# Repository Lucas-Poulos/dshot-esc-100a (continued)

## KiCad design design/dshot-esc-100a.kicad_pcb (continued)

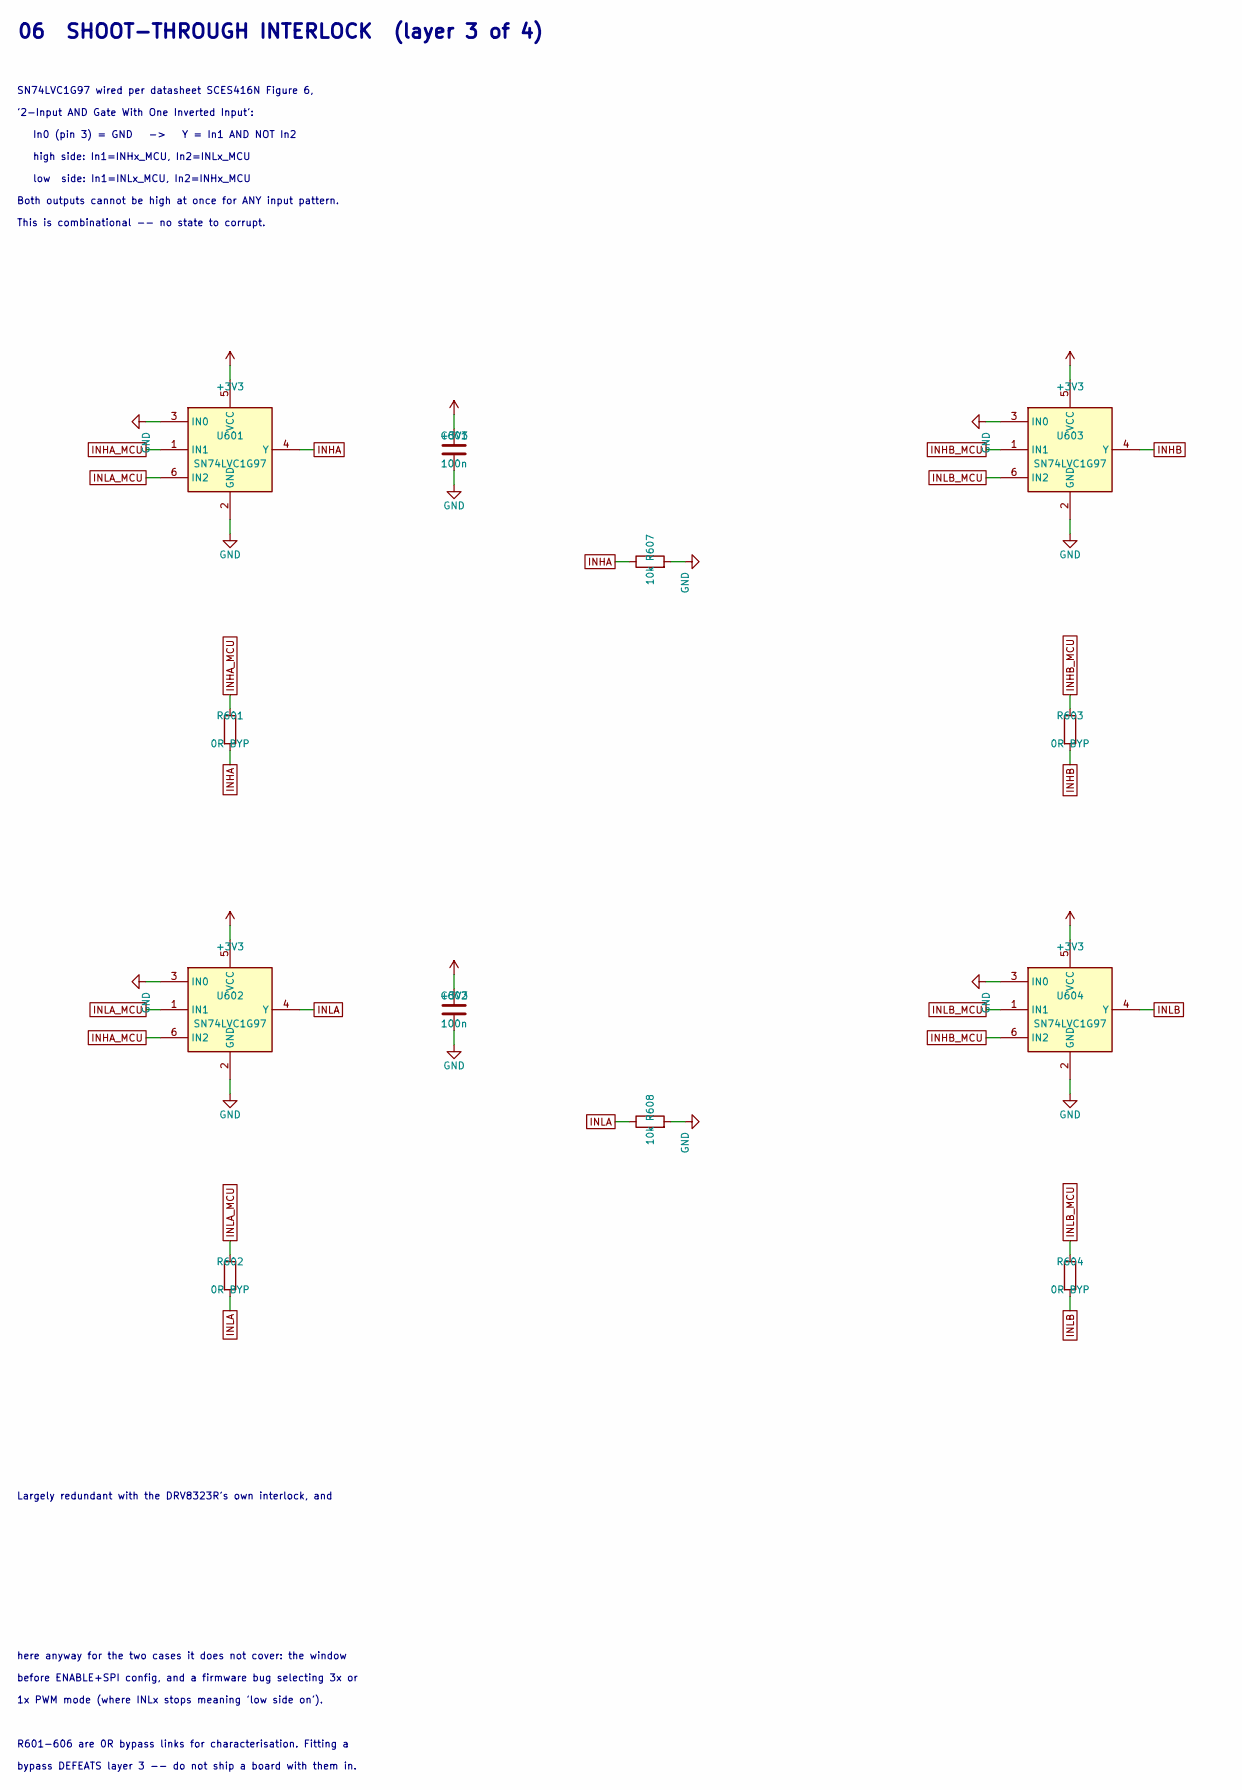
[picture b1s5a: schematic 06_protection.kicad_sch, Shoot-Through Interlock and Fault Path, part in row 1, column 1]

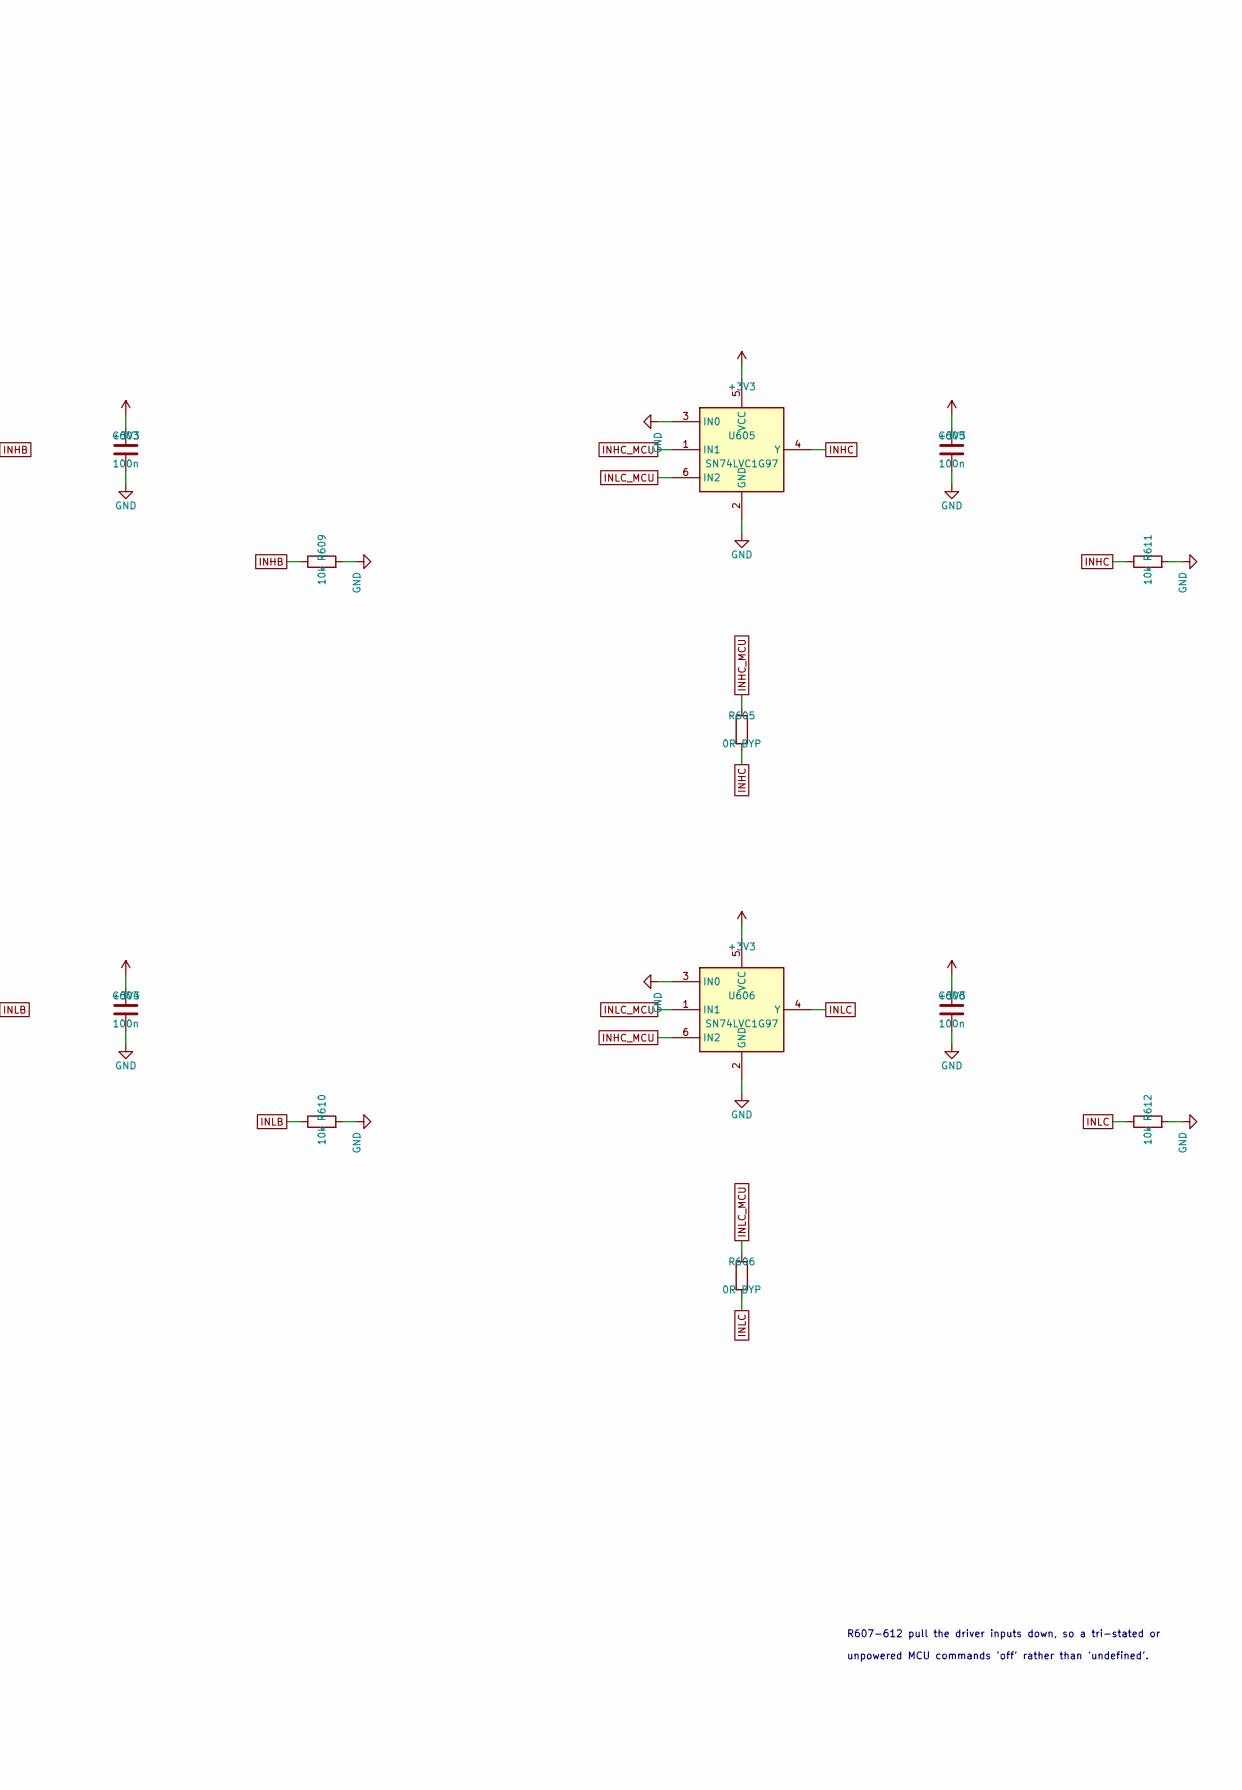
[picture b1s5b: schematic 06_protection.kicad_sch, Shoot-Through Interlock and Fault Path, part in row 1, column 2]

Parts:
C601, C602, C603, C604, C605, C606: 100n; C_0603_1608Metric; MPN CC0603KRX7R9BB104; LCSC C14663
R601, R602, R603, R604, R605, R606: 0R BYP; R_0603_1608Metric; MPN RCA030RLF; LCSC C22356631
R607, R608, R609, R610, R611, R612: 10k; R_0603_1608Metric; MPN FRC0603F1002TS; LCSC C2906982
U601, U602, U603, U604, U605, U606: SN74LVC1G97; SOT-23-6; MPN SN74LVC1G97DBVR; LCSC C128411

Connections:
+3V3: C601.1, C602.1, C603.1, C604.1, C605.1, C606.1, U601.5 (VCC), U602.5 (VCC), U603.5 (VCC), U604.5 (VCC), U605.5 (VCC), U606.5 (VCC); also elsewhere on the board
GND: C601.2, C602.2, C603.2, C604.2, C605.2, C606.2, R607.2, R608.2, R609.2, R610.2, R611.2, R612.2, U601.2 (GND), U601.3 (IN0), U602.2 (GND), U602.3 (IN0), U603.2 (GND), U603.3 (IN0), U604.2 (GND), U604.3 (IN0), U605.2 (GND), U605.3 (IN0), U606.2 (GND), U606.3 (IN0); also elsewhere on the board
INHA: R601.2, R607.1, U601.4 (Y); also elsewhere on the board
INHA_MCU: R601.1, U601.1 (IN1), U602.6 (IN2); also elsewhere on the board
INHB: R603.2, R609.1, U603.4 (Y); also elsewhere on the board
INHB_MCU: R603.1, U603.1 (IN1), U604.6 (IN2); also elsewhere on the board
INHC: R605.2, R611.1, U605.4 (Y); also elsewhere on the board
INHC_MCU: R605.1, U605.1 (IN1), U606.6 (IN2); also elsewhere on the board
INLA: R602.2, R608.1, U602.4 (Y); also elsewhere on the board
INLA_MCU: R602.1, U601.6 (IN2), U602.1 (IN1); also elsewhere on the board
INLB: R604.2, R610.1, U604.4 (Y); also elsewhere on the board
INLB_MCU: R604.1, U603.6 (IN2), U604.1 (IN1); also elsewhere on the board
INLC: R606.2, R612.1, U606.4 (Y); also elsewhere on the board
INLC_MCU: R606.1, U605.6 (IN2), U606.1 (IN1); also elsewhere on the board

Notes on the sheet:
high side: In1=INHx_MCU, In2=INLx_MCU
low side: In1=INLx_MCU, In2=INHx_MCU
before ENABLE+SPI config, and a firmware bug selecting 3x or
Largely redundant with the DRV8323R's own interlock, and
R601-606 are 0R bypass links for characterisation. Fitting a
06 SHOOT-THROUGH INTERLOCK (layer 3 of 4)
SN74LVC1G97 wired per datasheet SCES416N Figure 6,
bypass DEFEATS layer 3 -- do not ship a board with them in.
'2-Input AND Gate With One Inverted Input':
1x PWM mode (where INLx stops meaning 'low side on').
This is combinational -- no state to corrupt.
Both outputs cannot be high at once for ANY input pattern.
here anyway for the two cases it does not cover: the window
unpowered MCU commands 'off' rather than 'undefined'.
In0 (pin 3) = GND -> Y = In1 AND NOT In2
R607-612 pull the driver inputs down, so a tri-stated or

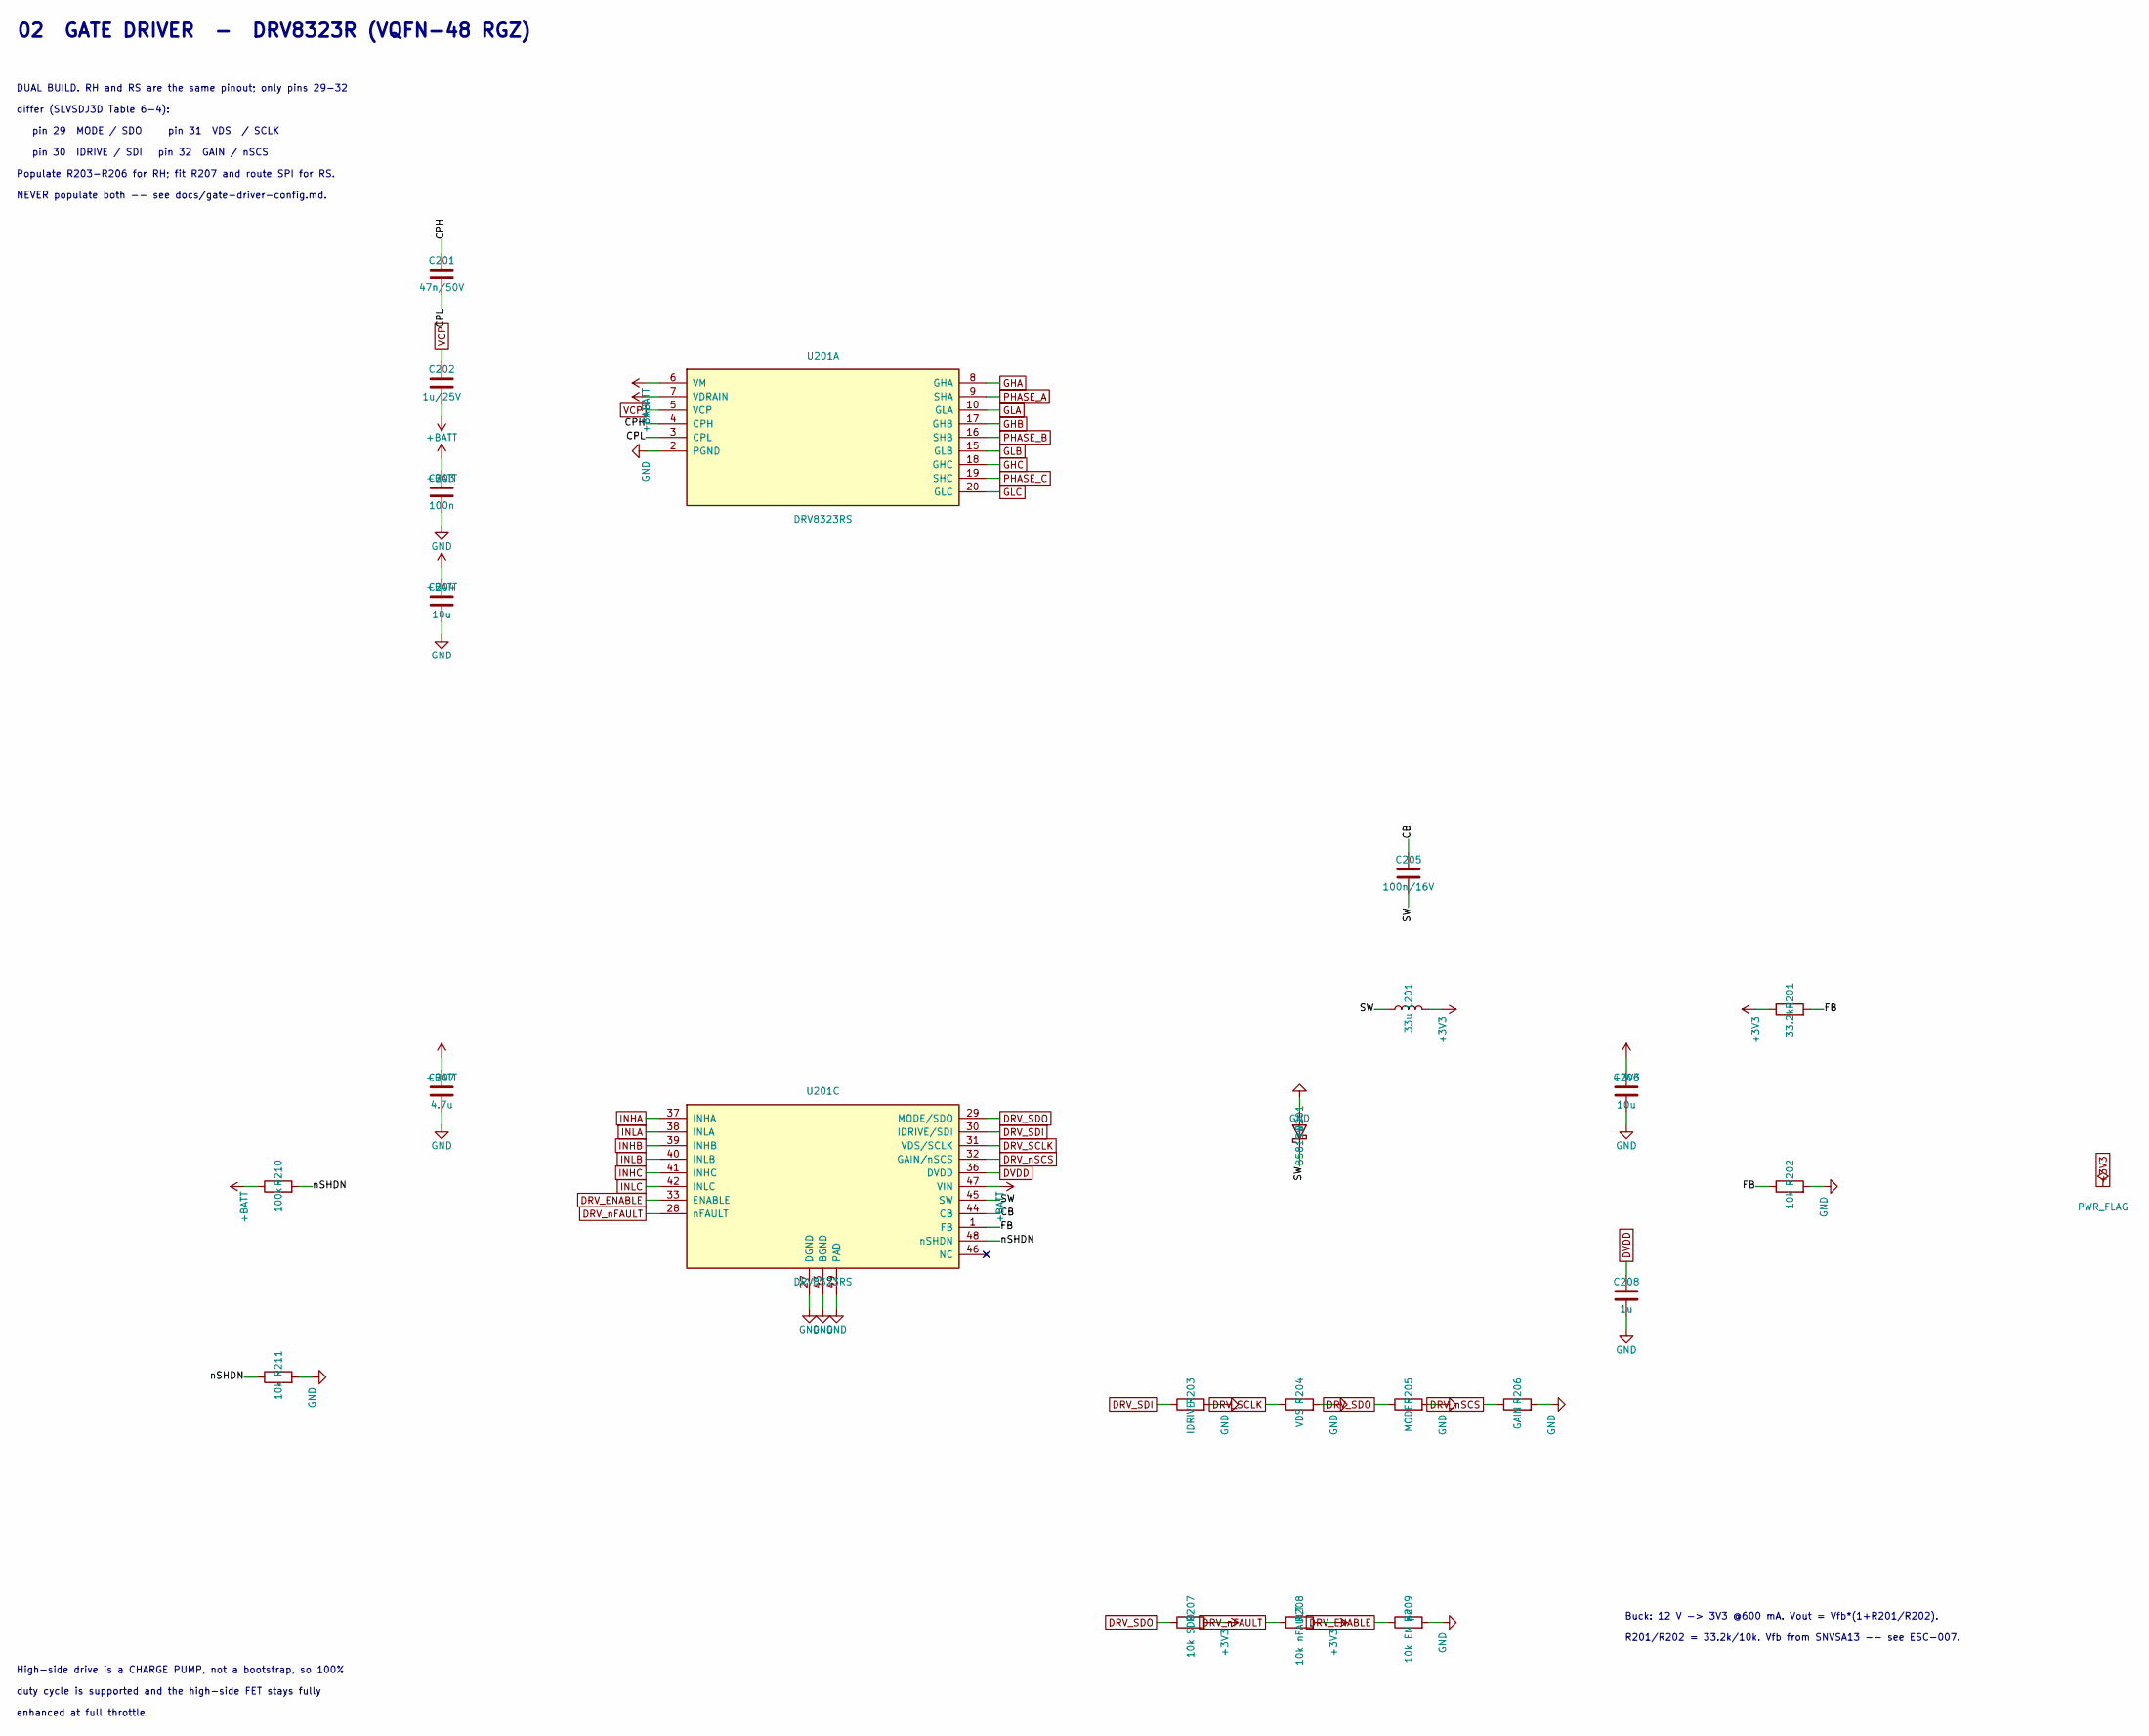
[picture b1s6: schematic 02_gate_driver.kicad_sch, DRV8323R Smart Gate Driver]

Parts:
C201: 47n/50V; C_0603_1608Metric; MPN CL10B473KB8NNNC; LCSC C1622
C202: 1u/25V; C_0603_1608Metric; MPN CL10B105KA8NNNC; LCSC C29936
C203: 100n; C_0603_1608Metric; MPN CC0603KRX7R9BB104; LCSC C14663
C204, C206: 10u; C_1210_3225Metric; MPN GRM32DR71E106KA12L; LCSC C77100
C205: 100n/16V; C_0603_1608Metric; MPN CC0603KRX7R9BB104; LCSC C14663
C207: 4.7u; C_0805_2012Metric; MPN CL21B475KAFNNNE; LCSC C98195
C208: 1u; C_0603_1608Metric; MPN CL10B105KA8NNNC; LCSC C29936
D201: B5819W; D_SOD-123; MPN B5819W SL; LCSC C8598
L201: 33u; L_7.3x7.3_H3.5; MPN SLS6D38S330MTT; LCSC C364136
R201: 33.2k; R_0603_1608Metric; MPN FRC0603F3322TS; LCSC C2933200
R202, R211: 10k; R_0603_1608Metric; MPN FRC0603F1002TS; LCSC C2906982
R203: IDRIVE; R_0603_1608Metric; MPN FRC0603F1002TS; LCSC C2906982
R204: VDS; R_0603_1608Metric; MPN FRC0603F1002TS; LCSC C2906982
R205: MODE; R_0603_1608Metric; MPN FRC0603F1002TS; LCSC C2906982
R206: GAIN; R_0603_1608Metric; MPN FRC0603F1002TS; LCSC C2906982
R207: 10k SDO; R_0603_1608Metric; MPN FRC0603F1002TS; LCSC C2906982
R208: 10k nFAULT; R_0603_1608Metric; MPN FRC0603F1002TS; LCSC C2906982
R209: 10k EN pd; R_0603_1608Metric; MPN FRC0603F1002TS; LCSC C2906982
R210: 100k; R_0603_1608Metric; MPN 0603WAF1003T5E; LCSC C25803
U201: DRV8323RS; Texas_RGZ0048A_VQFN-48-1EP_7x7mm_P0.5mm_EP5.15x5.15mm; MPN DRV8323RSRGZT; LCSC C2653553

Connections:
+3V3: C206.1, L201.2, R201.1, R207.2, R208.2; also elsewhere on the board
+BATT: C202.2, C203.1, C204.1, C207.1, R210.1, U201.6 (VM), U201.7 (VDRAIN), U201.47 (VIN); also elsewhere on the board
/Gate Driver/CB: C205.1, U201.44 (CB)
/Gate Driver/CPH: C201.1, U201.4 (CPH)
/Gate Driver/CPL: C201.2, U201.3 (CPL)
/Gate Driver/FB: R201.2, R202.1, U201.1 (FB)
/Gate Driver/SW: C205.2, D201.1 (K), L201.1, U201.45 (SW)
/Gate Driver/nSHDN: R210.2, R211.1, U201.48 (nSHDN)
DRV_ENABLE: R209.1, U201.33 (ENABLE); also elsewhere on the board
DRV_SCLK: R204.1, U201.31 (VDS/SCLK); also elsewhere on the board
DRV_SDI: R203.1, U201.30 (IDRIVE/SDI); also elsewhere on the board
DRV_SDO: R205.1, R207.1, U201.29 (MODE/SDO); also elsewhere on the board
DRV_nFAULT: R208.1, U201.28 (nFAULT); also elsewhere on the board
DRV_nSCS: R206.1, U201.32 (GAIN/nSCS); also elsewhere on the board
DVDD: C208.1, U201.36 (DVDD)
GHA: U201.8 (GHA); also elsewhere on the board
GHB: U201.17 (GHB); also elsewhere on the board
GHC: U201.18 (GHC); also elsewhere on the board
GLA: U201.10 (GLA); also elsewhere on the board
GLB: U201.15 (GLB); also elsewhere on the board
GLC: U201.20 (GLC); also elsewhere on the board
GND: C203.2, C204.2, C206.2, C207.2, C208.2, D201.2 (A), R202.2, R203.2, R204.2, R205.2, R206.2, R209.2, R211.2, U201.2 (PGND), U201.27 (DGND), U201.43 (BGND), U201.49 (PAD); also elsewhere on the board
INHA: U201.37 (INHA); also elsewhere on the board
INHB: U201.39 (INHB); also elsewhere on the board
INHC: U201.41 (INHC); also elsewhere on the board
INLA: U201.38 (INLA); also elsewhere on the board
INLB: U201.40 (INLB); also elsewhere on the board
INLC: U201.42 (INLC); also elsewhere on the board
PHASE_A: U201.9 (SHA); also elsewhere on the board
PHASE_B: U201.16 (SHB); also elsewhere on the board
PHASE_C: U201.19 (SHC); also elsewhere on the board
VCP: C202.1, U201.5 (VCP)

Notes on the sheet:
Populate R203-R206 for RH; fit R207 and route SPI for RS.
DUAL BUILD. RH and RS are the same pinout; only pins 29-32
Buck: 12 V -> 3V3 @600 mA. Vout = Vfb*(1+R201/R202).
differ (SLVSDJ3D Table 6-4):
02 GATE DRIVER - DRV8323R (VQFN-48 RGZ)
pin 29 MODE / SDO pin 31 VDS / SCLK
R201/R202 = 33.2k/10k. Vfb from SNVSA13 -- see ESC-007.
enhanced at full throttle.
NEVER populate both -- see docs/gate-driver-config.md.
duty cycle is supported and the high-side FET stays fully
High-side drive is a CHARGE PUMP, not a bootstrap, so 100%
pin 30 IDRIVE / SDI pin 32 GAIN / nSCS

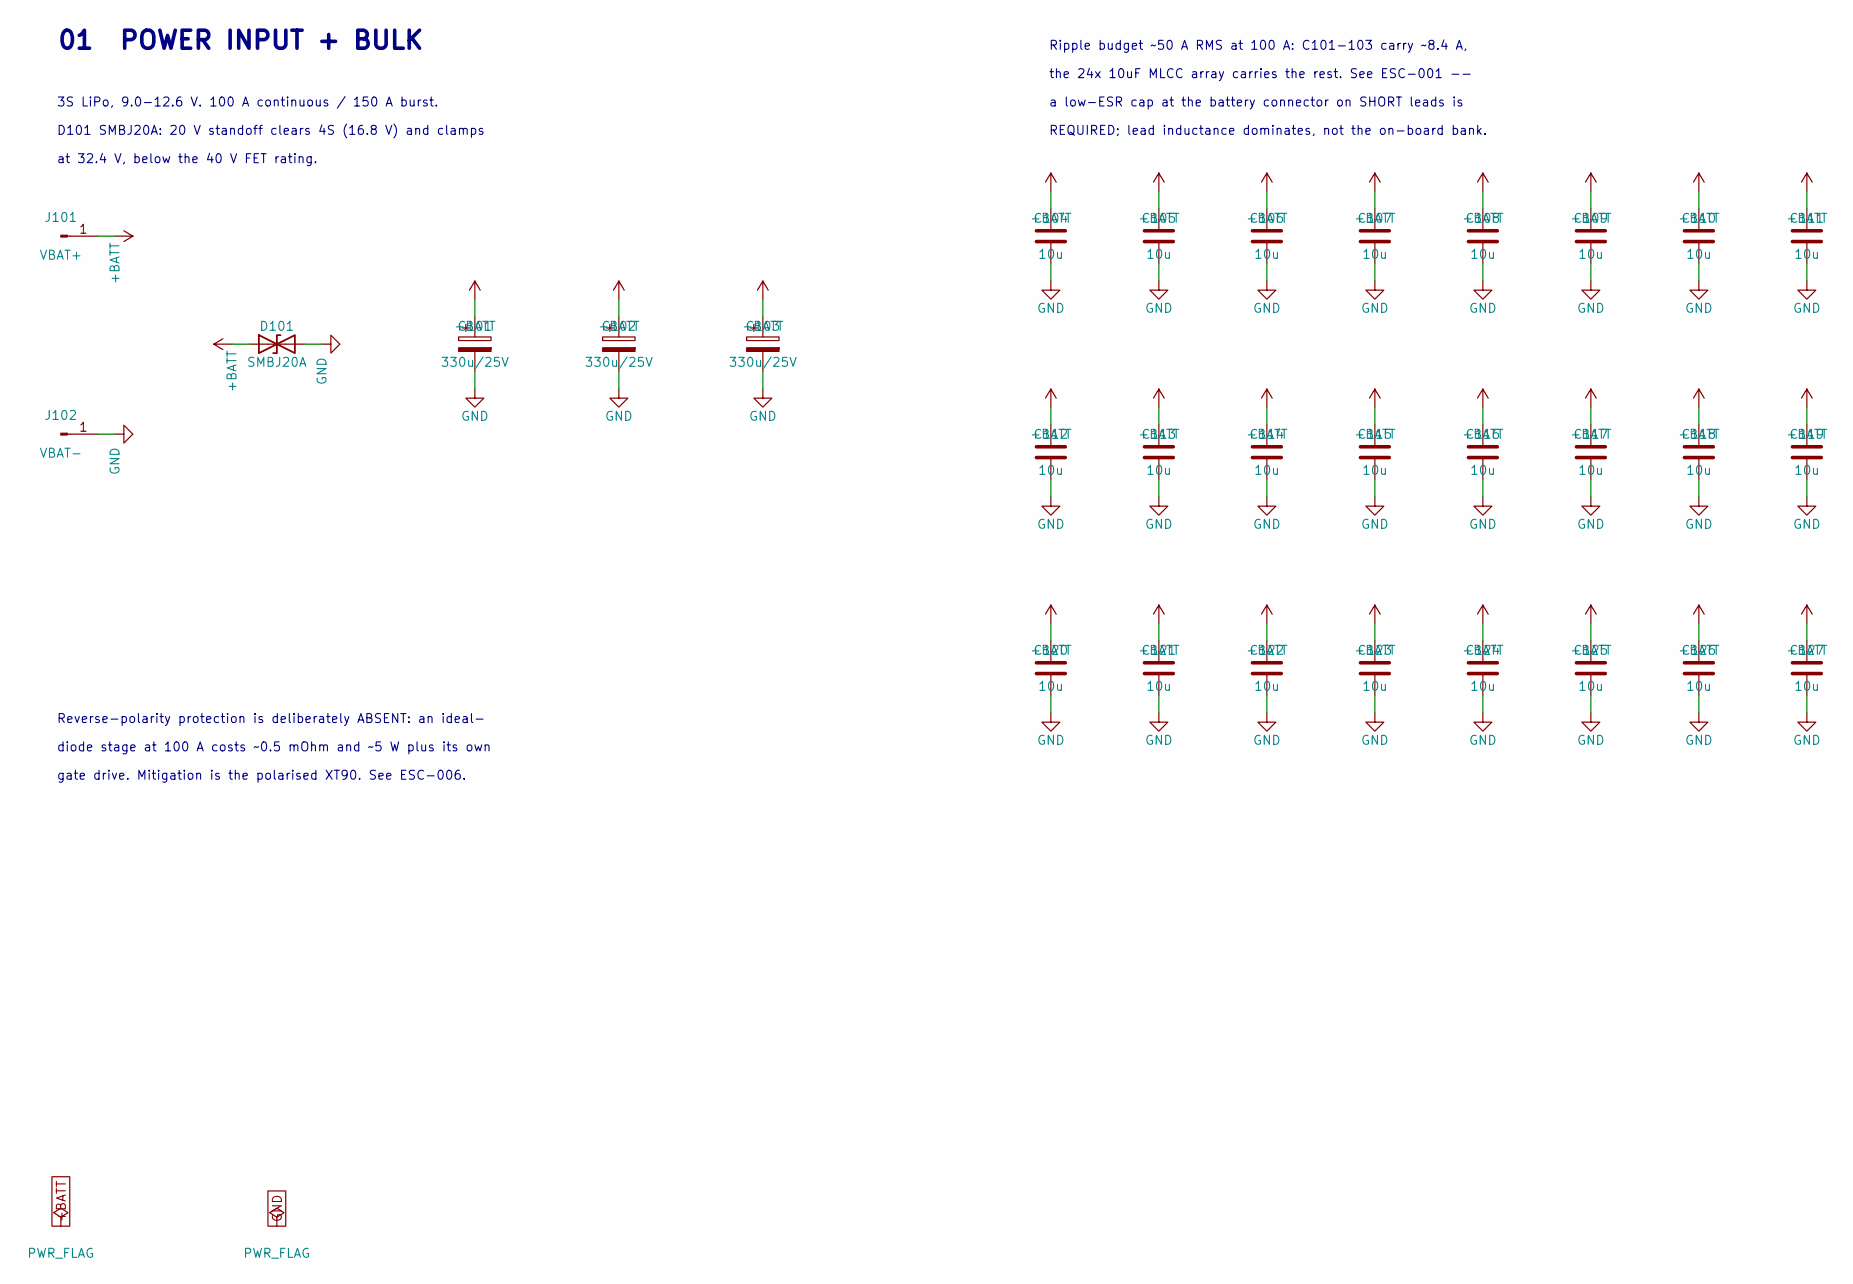
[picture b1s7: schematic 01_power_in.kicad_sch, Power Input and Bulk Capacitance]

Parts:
C101, C102, C103: 330u/25V; CP_Radial_D8.0mm_P3.50mm; MPN SPZ1EM331F11O00R; LCSC C160677
C104, C105, C106, C107, C108, C109, C110, C111, C112, C113, C114, C115, C116, C117, C118, C119, C120, C121, C122, C123, C124, C125, C126, C127: 10u; C_1210_3225Metric; MPN GRM32DR71E106KA12L; LCSC C77100
D101: SMBJ20A; D_SMB; MPN SMBJ20A; LCSC C364296
J101: VBAT+; HighCurrentTerminal_8AWG
J102: VBAT-; HighCurrentTerminal_8AWG

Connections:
+BATT: C101.1, C102.1, C103.1, C104.1, C105.1, C106.1, C107.1, C108.1, C109.1, C110.1, C111.1, C112.1, C113.1, C114.1, C115.1, C116.1, C117.1, C118.1, C119.1, C120.1, C121.1, C122.1, C123.1, C124.1, C125.1, C126.1, C127.1, D101.1 (A1), J101.1; also elsewhere on the board
GND: C101.2, C102.2, C103.2, C104.2, C105.2, C106.2, C107.2, C108.2, C109.2, C110.2, C111.2, C112.2, C113.2, C114.2, C115.2, C116.2, C117.2, C118.2, C119.2, C120.2, C121.2, C122.2, C123.2, C124.2, C125.2, C126.2, C127.2, D101.2 (A2), J102.1; also elsewhere on the board

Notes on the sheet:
Reverse-polarity protection is deliberately ABSENT: an ideal-
gate drive. Mitigation is the polarised XT90. See ESC-006.
at 32.4 V, below the 40 V FET rating.
a low-ESR cap at the battery connector on SHORT leads is
3S LiPo, 9.0-12.6 V. 100 A continuous / 150 A burst.
01 POWER INPUT + BULK
REQUIRED; lead inductance dominates, not the on-board bank.
Ripple budget ~50 A RMS at 100 A: C101-103 carry ~8.4 A,
diode stage at 100 A costs ~0.5 mOhm and ~5 W plus its own
the 24x 10uF MLCC array carries the rest. See ESC-001 --
D101 SMBJ20A: 20 V standoff clears 4S (16.8 V) and clamps

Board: 4 copper layers, 160 parts (53 on the bottom side), 72 nets, no tracks yet.

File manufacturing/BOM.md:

# Bill of materials

Generated from the schematic netlist by `scripts/gen_bom.py` on 2026-09-25. Do not edit by hand -- regenerate.

**43 distinct lines, 160 placements.** The schematic is fully wired and ERC-clean, so these quantities are real rather than provisional.

Prices and stock are deliberately absent -- they go stale within days. Refresh before a BOM lock with the `lcsc` skill.

---

## Sourcing notes

**The gate driver is the line to watch.** The design is laid out for both DRV8323R variants on one footprint -- only pins 29-32 differ (SLVSDJ3D Table 6-4):

| Part | LCSC | Stock | Price | Configured by |
|---|---|---:|---:|---|
| `DRV8323RSRGZT` | C2653553 | ~67 | $4.29 | SPI, from the MCU |
| `DRV8323RHRGZR` | C543035 | ~2338 | $2.39 | resistors R203-R206 |

RS is the default because it can set source and sink gate current independently, which is what produces the turn-off/turn-on asymmetry the dead-time budget relies on. RH cannot -- one pin sets both. An RH build is still safe but has less margin, and its resistor values are **not yet transcribed** (issue ESC-010). See `docs/gate-driver-config.md` before substituting.

Everything else is commodity: no part below has under ~1000 pieces at LCSC, and the FETs, MCU and logic all have multiple sources.

---

## Lines

| Qty | MPN | LCSC | Value | Package | Refs | Sheets |
|----:|-----|------|-------|---------|------|--------|
| 29 | `FRC0603F1002TS` | `C2906982` | 10k | R_0603_1608Metric | R202, R211, R313, R314, ... (+25) | Gate Driver, MCU, Power Stage, Protection, Sense |
| 26 | `GRM32DR71E106KA12L` | `C77100` | 10u | C_1210_3225Metric | C104, C105, C106, C107, ... (+22) | Gate Driver, Power Input |
| 12 | `FRC0805F4R70TS` | `C2933459` | 4.7 | R_0805_2012Metric | R301, R302, R303, R304, ... (+8) | Power Stage |
| 12 | `TPHR8504PL,L1Q(M` | `C5331611` | TPHR8504PL | PQFN-8-EP_6x5mm_P1.27mm_Generic | Q301, Q302, Q303, Q304, ... (+8) | Power Stage |
| 11 | `CC0603KRX7R9BB104` | `C14663` | 100n | C_0603_1608Metric | C203, C401, C402, C501, ... (+7) | Gate Driver, MCU, Protection, Sense |
| 7 | `B5819W SL` | `C8598` | B5819W | D_SOD-123 | D201, D301, D302, D303, D304, D305, D306 | Gate Driver, Power Stage |
| 6 | `RCA030RLF` | `C22356631` | 0 | R_0603_1608Metric | R325, R326, R327, R328, R329, R330 | Power Stage |
| 6 | `RCA030RLF` | `C22356631` | 0R BYP | R_0603_1608Metric | R601, R602, R603, R604, R605, R606 | Protection |
| 6 | `SN74LVC1G97DBVR` | `C128411` | SN74LVC1G97 | SOT-23-6 | U601, U602, U603, U604, U605, U606 | Protection |
| 5 | `FRC0603F1001TS` | `C2907002` | 1k | R_0603_1608Metric | R402, R504, R505, R506, R510 | MCU, Sense |
| 4 | `HoJLR2512-3W-1mR-1%` | `C2903470` | 1m | R_2512_6332Metric | RS301, RS302, RS303, RS304 | Power Stage |
| 3 | `SPZ1EM331F11O00R` | `C160677` | 330u/25V | CP_Radial_D8.0mm_P3.50mm | C101, C102, C103 | Power Input |
| 2 | `0603WAF1003T5E` | `C25803` | 100k | R_0603_1608Metric | R210, R511 | Gate Driver, Sense |
| 2 | `CL21B475KAFNNNE` | `C98195` | 4.7u | C_0805_2012Metric | C207, C403 | Gate Driver, MCU |
| 1 | `-` | `-` | PHASE_A | SolderWire-2.5sqmm_1x01_D2.4mm_OD3.6mm_Relief | J301 | Power Stage |
| 1 | `-` | `-` | PHASE_B | SolderWire-2.5sqmm_1x01_D2.4mm_OD3.6mm_Relief | J302 | Power Stage |
| 1 | `-` | `-` | PHASE_C | SolderWire-2.5sqmm_1x01_D2.4mm_OD3.6mm_Relief | J303 | Power Stage |
| 1 | `-` | `-` | SWD | PinHeader_2x05_P1.27mm_Vertical | J401 | MCU |
| 1 | `-` | `-` | SIGNAL | PinHeader_1x04_P2.54mm_Vertical | J402 | MCU |
| 1 | `-` | `-` | VBAT+ | SolderWire-2.5sqmm_1x01_D2.4mm_OD3.6mm_Relief | J101 | Power Input |
| 1 | `-` | `-` | VBAT- | SolderWire-2.5sqmm_1x01_D2.4mm_OD3.6mm_Relief | J102 | Power Input |
| 1 | `CC0603KRX7R9BB104` | `C14663` | 100n/16V | C_0603_1608Metric | C205 | Gate Driver |
| 1 | `CC0603KRX7R9BB104` | `C14663` | 100n VREF+ | C_0603_1608Metric | C404 | MCU |
| 1 | `CC0603KRX7R9BB104` | `C14663` | 100n NRST | C_0603_1608Metric | C406 | MCU |
| 1 | `CC0603KRX7R9BB104` | `C14663` | 100n VREF | C_0603_1608Metric | C503 | Sense |
| 1 | `CL10B105KA8NNNC` | `C29936` | 1u/25V | C_0603_1608Metric | C202 | Gate Driver |
| 1 | `CL10B105KA8NNNC` | `C29936` | 1u | C_0603_1608Metric | C208 | Gate Driver |
| 1 | `CL10B105KA8NNNC` | `C29936` | 1u VREF+ | C_0603_1608Metric | C405 | MCU |
| 1 | `CL10B473KB8NNNC` | `C1622` | 47n/50V | C_0603_1608Metric | C201 | Gate Driver |
| 1 | `DRV8323RSRGZT` | `C2653553` | DRV8323RS | Texas_RGZ0048A_VQFN-48-1EP_7x7mm_P0.5mm_EP5.15x5.15mm_ThermalVias | U201 | Gate Driver |
| 1 | `FRC0603F1002TS` | `C2906982` | IDRIVE | R_0603_1608Metric | R203 | Gate Driver |
| 1 | `FRC0603F1002TS` | `C2906982` | VDS | R_0603_1608Metric | R204 | Gate Driver |
| 1 | `FRC0603F1002TS` | `C2906982` | MODE | R_0603_1608Metric | R205 | Gate Driver |
| 1 | `FRC0603F1002TS` | `C2906982` | GAIN | R_0603_1608Metric | R206 | Gate Driver |
| 1 | `FRC0603F1002TS` | `C2906982` | 10k SDO | R_0603_1608Metric | R207 | Gate Driver |
| 1 | `FRC0603F1002TS` | `C2906982` | 10k nFAULT | R_0603_1608Metric | R208 | Gate Driver |
| 1 | `FRC0603F1002TS` | `C2906982` | 10k EN pd | R_0603_1608Metric | R209 | Gate Driver |
| 1 | `FRC0603F3322TS` | `C2933200` | 33.2k | R_0603_1608Metric | R201 | Gate Driver |
| 1 | `NCP18XH103F03RB` | `C13564` | 10k NTC | R_0603_1608Metric | R513 | Sense |
| 1 | `SLS6D38S330MTT` | `C364136` | 33u | L_7.3x7.3_H3.5 | L201 | Gate Driver |
| 1 | `SMBJ20A` | `C364296` | SMBJ20A | D_SMB | D101 | Power Input |
| 1 | `STM32G071CBT6` | `C432212` | STM32G071CBT6 | LQFP-48_7x7mm_P0.5mm | U401 | MCU |
| 1 | `XL-1608UGC-04` | `C965804` | green | LED_0603_1608Metric | D401 | MCU |

---

## Lines needing attention

| MPN | Note |
|---|---|
| `GRM32DR71E106KA12L` | 24 off. Derates to ~5-6 uF at 12 V bias - ESC-001 |
| `TPHR8504PL,L1Q(M` | 12 off, 2 per switch position. 40 V on a 12.6 V bus is deliberate - see docs/architecture.md |
| `SN74LVC1G97DBVR` | Shoot-through interlock. Wired per SCES416N Fig 6 |
| `HoJLR2512-3W-1mR-1%` | 4 in parallel = 0.25 mOhm. Needs a Kelvin sense tap in layout - ESC-005 |
| `SPZ1EM331F11O00R` | Through-hole radial. ~2.8 A ripple each - ESC-001 |
| `DRV8323RSRGZT` | SPI variant. RH (C543035) is pin-compatible - see docs/gate-driver-config.md before substituting |
| `STM32G071CBT6` | 48-pin part is REQUIRED: it is the only one that frees PB12/TIM1_BKIN. Symbol is KiCad's G081CBTx renamed |

## Before ordering

1. Wire the schematic -- quantities here are pre-wiring estimates.
2. Refresh stock for every line; flag anything under 10x requirement.
3. Record a second-source C-number for each thin line in that part's `manufacturing/parts/{Vendor}/{MPN}/{MPN}.md`.
4. Resolve everything in `manufacturing/stm32mp157-devkit/ISSUES.md` or defer it explicitly.
5. Re-run `python3 scripts/verify_project.py`.
6. Re-check stock immediately before placing the order -- do not order against numbers from a previous session.

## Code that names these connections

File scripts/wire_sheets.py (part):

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def wire_04_mcu(sheet: Sheet, cache: SymbolCache) -> None:
    """Pins are addressed by NUMBER, not name.

    PA9 and PA10 each appear twice in the 48-pin symbol -- as the dedicated
    pins 29/32 and again as the remappable PA11/PA12 pads 33/34. Addressing
    by name would be ambiguous, and picking the wrong one puts a PWM output
    on an unbonded pad.
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    w.power("R401", "1", V3V3)

    # --- TIM1 complementary PWM -> interlock (sheet 06) ---
    w.rail(INH_MCU["A"], (M, "32"))                               # PA10 TIM1_CH3
    w.rail(INL_MCU["A"], (M, "20"))                               # PB1  TIM1_CH3N
    w.rail(INH_MCU["B"], (M, "29"))                               # PA9  TIM1_CH2
    w.rail(INL_MCU["B"], (M, "19"))                               # PB0  TIM1_CH2N
    w.rail(INH_MCU["C"], (M, "28"))                               # PA8  TIM1_CH1
    w.rail(INL_MCU["C"], (M, "18"))                               # PA7  TIM1_CH1N
    # PA11 / PA12 pads are unused because NO_PA11_PA12_REMAP is set
    w.no_connect(M, "33")
    w.no_connect(M, "34")

    # --- sensorless comparator inputs ---
    w.rail(BEMF["A"], (M, "46"))       # PB7 COMP2_INM IO2
    w.rail(BEMF["B"], (M, "42"))       # PB3 COMP2_INM IO1
    w.rail(BEMF["C"], (M, "13"))       # PA2 COMP2_INM IO3
    w.rail(V_NEUTRAL, (M, "14"))       # PA3 COMP2_INP IO3

    # --- ADC ---
    w.rail(ADC_BUSV, (M, "15"))      # PA4 ADC_IN4
    w.rail(ADC_CURRENT, (M, "17"))         # PA6 ADC_IN6
    w.rail(ADC_TEMP, (M, "12"))       # PA1 ADC_IN1

    # --- gate driver control ---
    w.rail(DRV_NSCS, (M, "11"))        # PA0
    w.rail(DRV_SDO, (M, "21"))         # PB2
    w.rail(DRV_SCLK, (M, "22"))        # PB10
    w.rail(DRV_SDI, (M, "23"))         # PB11
    w.rail(DRV_NFAULT, (M, "24"))      # PB12 TIM1_BKIN
    w.rail(DRV_ENABLE, (M, "25"))      # PB13
    w.rail(DRV_CAL, (M, "26"))         # PB14

    # --- host interface + debug ---
    w.rail(DSHOT_IN, (M, "43"))        # PB4 TIM3_CH1 + DMA1_CH1
    w.rail(TELEM, (M, "45"))           # PB6 USART1 AF0, one-wire
    w.rail(SWDIO, (M, "35"))           # PA13
    w.rail(SWCLK, (M, "36"))           # PA14
    w.rail(LED_STATUS, (M, "30"))      # PC6

    # unused pins
    for pin in ("1", "2", "3", "8", "9", "16", "27", "31", "37",
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
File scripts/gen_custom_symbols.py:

#!/usr/bin/env python3
"""Generate the project-local symbol library: design/lib/dshot-esc-100a.kicad_sym

Two symbols, for two different reasons.

DRV8323R
    KiCad 10 ships no DRV83xx smart gate driver at all (Driver_Motor has
    DRV8308/8311/8412/8434/8461 and nothing else), so this is built from
    scratch. Every pin below is transcribed from **Table 6-4, "Pin
    Functions - 48-Pin DRV8323R Devices"** of the DRV832x datasheet
    SLVSDJ3D (rev D, March 2022), pages 10-11.

    This board is a dual RH/RS build. Table 6-4 gives both columns and
    they are identical for 44 of the 48 pins -- **only pins 29-32 differ**:

        pin   DRV8323RH        DRV8323RS
        29    MODE             SDO
        30    IDRIVE           SDI
        31    VDS              SCLK
        32    GAIN             nSCS

    Those four carry both names in the symbol, because the schematic has
    to show both the resistor network and the SPI routing.

STM32G071CBTx
    KiCad has E/G/K/R-package G071 symbols but no C (48-pin) one. It does
    have STM32G081CBTx, and the G081CB is the same die and the same
    package bonding as the G071CB -- ST documents both in DS12232, and the
    difference is the AES accelerator, which has no pins. So rather than
    hand-transcribing 48 pins (and risking a transcription error on a
    board where a swapped PWM pin destroys the bridge), the stock symbol
    is copied and renamed.
"""
from __future__ import annotations

import re
import subprocess
import sys
from pathlib import Path

from kicad_symlib import Pin, Unit, emit_symbol, upsert, split_symbols

ROOT = Path(__file__).resolve().parent.parent
LIB = ROOT / "design" / "lib" / "dshot-esc-100a.kicad_sym"
STOCK = Path("/Applications/KiCad/KiCad.app/Contents/SharedSupport/symbols")

DS_DRV = "https://www.ti.com/lit/ds/symlink/drv8323.pdf"
DS_STM = "https://www.st.com/resource/en/datasheet/stm32g071cb.pdf"

FP_DRV = ("Package_DFN_QFN:Texas_RGZ0048A_VQFN-48-1EP_7x7mm_P0.5mm"
          "_EP5.15x5.15mm")
FP_STM = "Package_QFP:LQFP-48_7x7mm_P0.5mm"

# --------------------------------------------------------------------------
# DRV8323R -- SLVSDJ3D Table 6-4. (name, pad, electrical type)
# --------------------------------------------------------------------------

# Unit A: gate drive + charge pump + power. The high-current half.
UNIT_A_LEFT = [
    Pin("VM", "6", "power_in"),
    Pin("VDRAIN", "7", "input"),
    Pin("VCP", "5", "passive"),
    Pin("CPH", "4", "passive"),
    Pin("CPL", "3", "passive"),
    Pin("PGND", "2", "power_in"),
]
UNIT_A_RIGHT = [
    Pin("GHA", "8", "output"),
    Pin("SHA", "9", "bidirectional"),
    Pin("GLA", "10", "output"),
    Pin("GHB", "17", "output"),
    Pin("SHB", "16", "bidirectional"),
    Pin("GLB", "15", "output"),
    Pin("GHC", "18", "output"),
    Pin("SHC", "19", "bidirectional"),
    Pin("GLC", "20", "output"),
]

# Unit B: the three current-shunt amplifiers.
UNIT_B_LEFT = [
    Pin("SPA", "11", "input"),
    Pin("SNA", "12", "input"),
    Pin("SPB", "14", "input"),
    Pin("SNB", "13", "input"),
    Pin("SPC", "21", "input"),
    Pin("SNC", "22", "input"),
]
UNIT_B_RIGHT = [
    Pin("SOA", "25", "output"),
    Pin("SOB", "24", "output"),
    Pin("SOC", "23", "output"),
    Pin("VREF", "26", "power_in"),
    Pin("CAL", "34", "input"),
    Pin("AGND", "35", "power_in"),
]

# Unit C: logic inputs, config/SPI, the buck regulator, grounds.
UNIT_C_LEFT = [
    Pin("INHA", "37", "input"),
    Pin("INLA", "38", "input"),
    Pin("INHB", "39", "input"),
    Pin("INLB", "40", "input"),
    Pin("INHC", "41", "input"),
    Pin("INLC", "42", "input"),
    Pin("ENABLE", "33", "input"),
    Pin("nFAULT", "28", "open_collector"),
]
UNIT_C_RIGHT = [
    # pins 29-32: RH name / RS name (Table 6-4)
    Pin("MODE/SDO", "29", "bidirectional"),
    Pin("IDRIVE/SDI", "30", "input"),
    Pin("VDS/SCLK", "31", "input"),
    Pin("GAIN/nSCS", "32", "input"),
    Pin("DVDD", "36", "power_out"),
    Pin("VIN", "47", "power_in"),
    Pin("SW", "45", "output"),
    Pin("CB", "44", "passive"),
    Pin("FB", "1", "input"),
    Pin("nSHDN", "48", "input"),
    Pin("NC", "46", "no_connect"),
]
UNIT_C_BOTTOM = [
    Pin("DGND", "27", "power_in"),
    Pin("BGND", "43", "power_in"),
    Pin("PAD", "49", "power_in"),
]

DRV_PROPS = {
    "Footprint": FP_DRV,
    "Datasheet": DS_DRV,
    "Description": ("6-60V three-phase smart gate driver, 3x CSA, "
                    "600mA buck, VQFN-48 RGZ"),
    "MPN": "DRV8323RSRGZT",
    "Manufacturer": "Texas Instruments",
    "LCSC": "C2653553",
    "MPN_ALT": "DRV8323RHRGZR",
    "LCSC_ALT": "C543035",
}


def build_drv() -> str:
    units = [
        Unit(left=UNIT_A_LEFT, right=UNIT_A_RIGHT),
        Unit(left=UNIT_B_LEFT, right=UNIT_B_RIGHT),
        Unit(left=UNIT_C_LEFT, right=UNIT_C_RIGHT, bottom=UNIT_C_BOTTOM),
    ]
    text, pinmaps = emit_symbol("DRV8323R", units, DRV_PROPS)
    return text, pinmaps


def build_stm() -> str:
    """Copy MCU_ST_STM32G0:STM32G081CBTx -> STM32G071CBTx."""
    src = (STOCK / "MCU_ST_STM32G0.kicad_sym").read_text()
    blocks = split_symbols(src)
    key = "STM32G081CBTx"
    if key not in blocks:
        sys.exit(f"FATAL: {key} not found in stock MCU_ST_STM32G0.kicad_sym")
    body = blocks[key]
    if "extends" in body.split("\n")[1]:
        sys.exit(f"FATAL: {key} uses 'extends'; must be flattened first")
    # Rename the symbol and its nested unit sub-symbols in one pass.
    body = body.replace("STM32G081CBTx", "STM32G071CBTx")
    # Point Value / Footprint / Datasheet at the part we actually order.
    body = re.sub(r'\(property "Footprint" "[^"]*"',
                  f'(property "Footprint" "{FP_STM}"', body, count=1)
    body = re.sub(r'\(property "Datasheet" "[^"]*"',
                  f'(property "Datasheet" "{DS_STM}"', body, count=1)
    return body


def normalize(path: Path) -> None:
    """Let KiCad itself rewrite the library into its canonical form.

    Our emitter produces semantically correct output, but KiCad sorts pins
    into its own order when it saves. Without this step the file churns
    every time anyone opens the library in the GUI, and a 400-line
    reordering diff hides real changes. Running the upgrade here makes the
    generator byte-idempotent against KiCad 10.0.5.

    Side effect: it rewrites (generator ...) to "kicad_symbol_editor",
    which is accurate -- the file is in that tool's format.
    """
    r = subprocess.run(["kicad-cli", "sym", "upgrade", "--force", str(path)],
                       capture_output=True, text=True)
    if r.returncode != 0:
        sys.exit(f"FATAL: kicad-cli rejected the library:\n{r.stderr}")


def main() -> None:
    verify = "--verify" in sys.argv

    drv_text, pinmaps = build_drv()
    pads = []
    for unit in (UNIT_A_LEFT + UNIT_A_RIGHT + UNIT_B_LEFT + UNIT_B_RIGHT
                 + UNIT_C_LEFT + UNIT_C_RIGHT + UNIT_C_BOTTOM):
        pads.append(unit.number)

    ok = True
    if len(pads) != len(set(pads)):
        dupes = {p for p in pads if pads.count(p) > 1}
        print(f"FAIL: duplicate pads {sorted(dupes)}")
        ok = False
    expected = {str(n) for n in range(1, 50)}     # 48 pins + pad 49
    missing = expected - set(pads)
    extra = set(pads) - expected
    if missing:
        print(f"FAIL: missing pads {sorted(missing, key=int)}")
        ok = False
    if extra:
        print(f"FAIL: unexpected pads {sorted(extra)}")
        ok = False
    print(f"DRV8323R: {len(pads)} pads across 3 units "
          f"({'OK' if ok else 'BROKEN'})")

    stm_text = build_stm()
    n_stm = len(re.findall(r'\(number "', stm_text))
    if n_stm != 48:
        print(f"FAIL: STM32G071CBTx has {n_stm} pins, expected 48")
        ok = False
    print(f"STM32G071CBTx: {n_stm} pins (copied from STM32G081CBTx)")

    if not ok:
        sys.exit(1)
    if verify:
        print("\n--verify only, nothing written")
        return

    upsert(LIB, drv_text, "DRV8323R")
    upsert(LIB, stm_text, "STM32G071CBTx")
    normalize(LIB)
    print(f"\nwrote {LIB.relative_to(ROOT)}")


if __name__ == "__main__":
    main()
